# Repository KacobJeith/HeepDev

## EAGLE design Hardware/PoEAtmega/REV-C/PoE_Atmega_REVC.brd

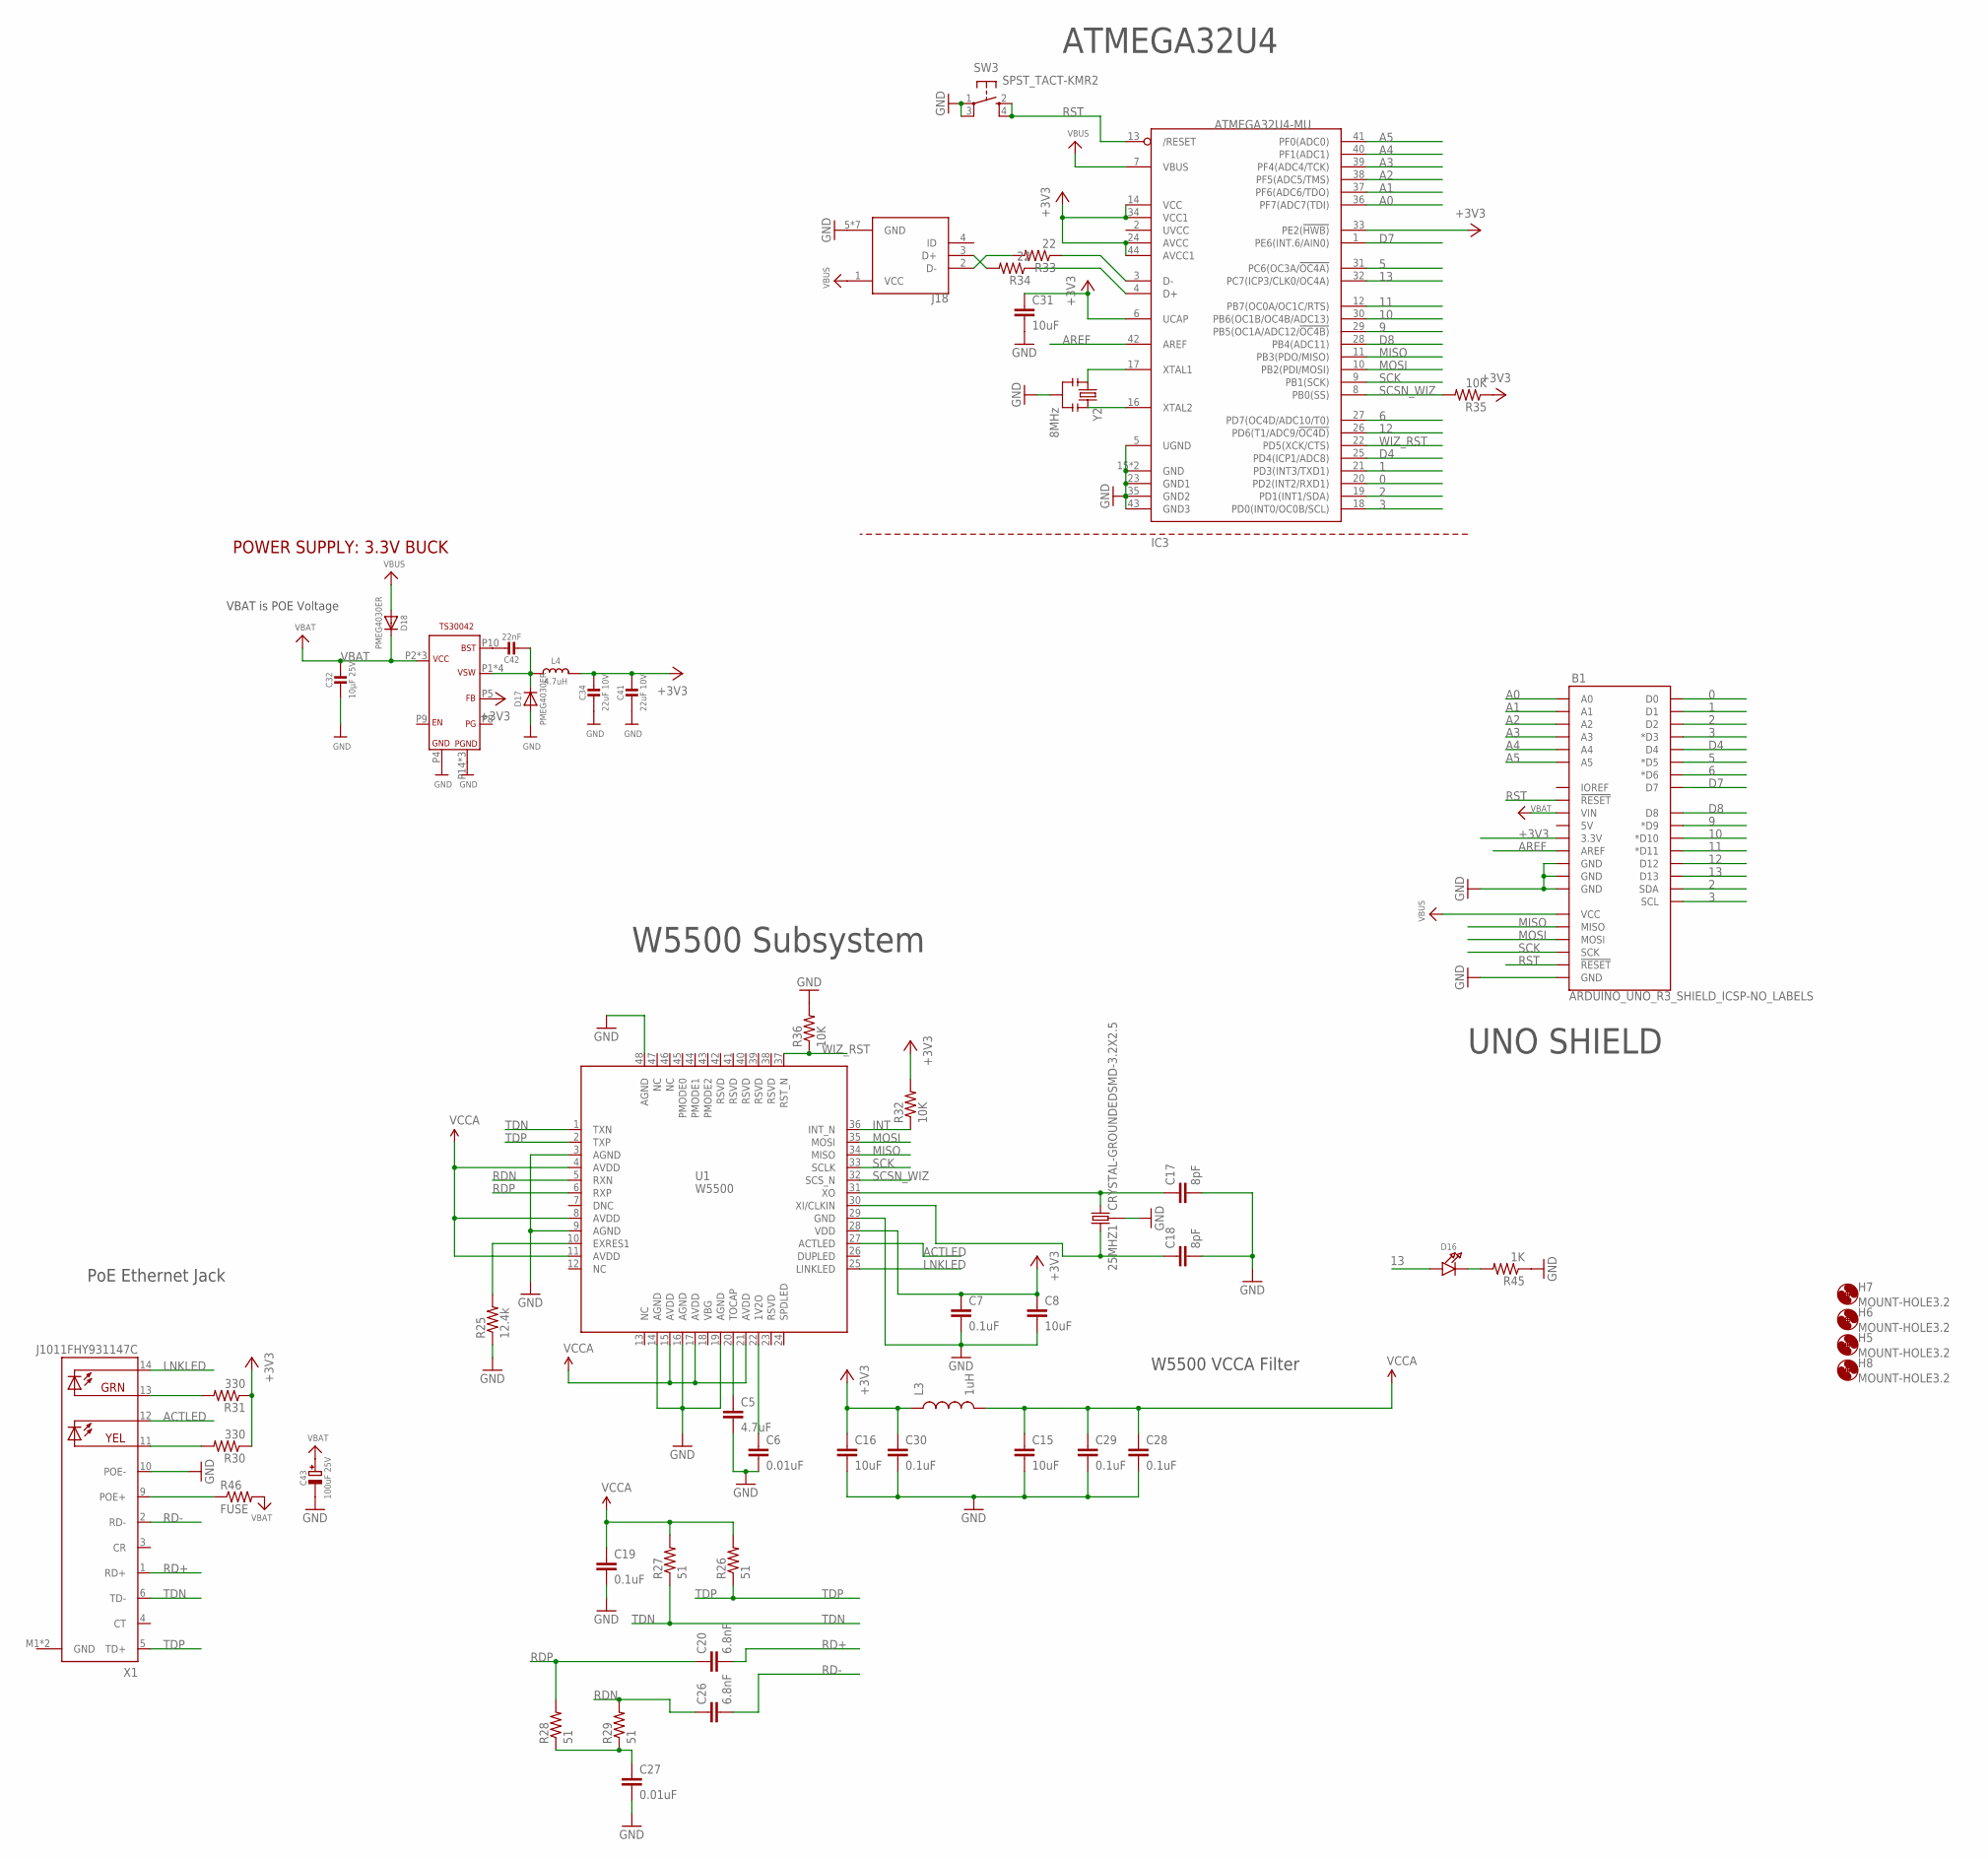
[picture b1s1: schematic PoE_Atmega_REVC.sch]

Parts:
25MHZ1: CRYSTAL-GROUNDEDSMD-3.2X2.5; CRYSTAL-SMD-3.2X2.5MM
B1: ARDUINO_UNO_R3_SHIELD_ICSP-NO_LABELS; UNO_R3_SHIELD_ICSP_NOLABELS
C5: 4.7uF; 0603-CAP
C6, C27: 0.01uF; 0603-CAP
C7, C19, C28, C29, C30: 0.1uF; 0603-CAP
C8, C15, C16, C31: 10uF; 0603-CAP
C17, C18: 8pF; 0603-CAP
C20, C26: 6.8nF; 0603-CAP
C32: 10µF 25V; 0603-MINI
C34, C41: 22uF 10V; 0603-MINI
C42: 22nF; 0603-MINI
C43: 100uF 25V; PANASONIC_D
D16: LED0805_NOOUTLINE; CHIPLED_0805_NOOUTLINE
D17, D18: PMEG4030ER; SOD-123
H5, H6, H7, H8: MOUNT-HOLE3.2; 3,2
IC3: ATMEGA32U4-MU; TQFN44_7MM
J18: 10103594-0001LF; FCI_10103594-0001LF
L3: 1uH; 0603
L4: 4.7uH; INDUCTOR_5X5MM_TDK_VLC5045
R25: 12.4k; 0603-RES
R26, R27, R28, R29: 51; 0603-RES
R30, R31: 330; 0603-RES
R32, R35, R36: 10K; 0603-RES
R33, R34: 22; 0603-RES
R45: 1K; 0603-RES
R46: FUSE; 0603-RES
SW3: SPST_TACT-KMR2; KMR2
U1: W5500
U$44: BUCK_CONVERTER; QFN-16
X1: J1011FHY931147C; HANRUN_POE
Y2: 8MHz; RESONATOR-SMD

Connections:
0: B1.RX (D0), IC3.20 (PD2(INT2/RXD1))
1: B1.TX (D1), IC3.21 (PD3(INT3/TXD1))
2: B1.D2, B1.SDA, IC3.19 (PD1(INT1/SDA))
3: B1.D3 (*D3), B1.SCL, IC3.18 (PD0(INT0/OC0B/SCL))
5: B1.D5 (*D5), IC3.31 (PC6(OC3A/!OC4A))
6: B1.D6 (*D6), IC3.27 (PD7(OC4D/ADC10/T0))
9: B1.D9 (*D9), IC3.29 (PB5(OC1A/ADC12/!OC4B))
10: B1.D10 (*D10), IC3.30 (PB6(OC1B/OC4B/ADC13))
11: B1.D11 (*D11), IC3.12 (PB7(OC0A/OC1C/RTS))
12: B1.D12, IC3.26 (PD6(T1/ADC9/!OC4D))
13: B1.D13, D16.A, IC3.32 (PC7(ICP3/CLK0/OC4A))
+3V3: B1.3.3V, C7.1, C8.1, C16.1, C30.1, C31.1, C34.1, C41.1, IC3.6 (UCAP), IC3.14 (VCC), IC3.24 (AVCC), IC3.33 (PE2(!HWB)), IC3.34 (VCC1), IC3.44 (AVCC1), L3.1, L4.P$2 (2), R30.1, R31.1, R32.2, R35.1, U1.28 (VDD), U$44.P5 (FB)
A0: B1.A0, IC3.36 (PF7(ADC7(TDI))
A1: B1.A1, IC3.37 (PF6(ADC6/TDO))
A2: B1.A2, IC3.38 (PF5(ADC5/TMS))
A3: B1.A3, IC3.39 (PF4(ADC4/TCK))
A4: B1.A4, IC3.40 (PF1(ADC1))
A5: B1.A5, IC3.41 (PF0(ADC0))
ACTLED: U1.27 (ACTLED), X1.12 (YEL-C)
AREF: B1.AREF, IC3.42 (AREF)
D4: B1.D4, IC3.25 (PD4(ICP1/ADC8))
D7: B1.D7, IC3.1 (PE6(INT.6/AIN0))
D8: B1.D8, IC3.28 (PB4(ADC11))
D+2: IC3.4 (D+), R34.1
D-2: IC3.3 (D-), R33.1
GND: 25MHZ1.2 (3), 25MHZ1.4 (3), B1.GND@0 (GND), B1.GND@1 (GND), B1.GND@2 (GND), B1.GND_ICSP (GND), C5.2, C6.2, C7.2, C8.2, C15.2, C16.2, C17.2, C18.2, C19.2, C27.2, C28.2, C29.2, C30.2, C31.2, C32.2, C34.2, C41.2, C43.-, D17.A, IC3.5 (UGND), IC3.15 (GND), IC3.23 (GND1), IC3.35 (GND2), IC3.43 (GND3), IC3.THERMAL (GND), J18.5 (GND), J18.P1 (GND), J18.P2 (GND), J18.P3 (GND), J18.P4 (GND), J18.P5 (GND), J18.P6 (GND), R25.1, R36.2, R45.1, SW3.1, SW3.3 (P1), U1.3 (AGND), U1.9 (AGND), U1.14 (AGND), U1.16 (AGND), U1.19 (AGND), U1.29 (GND), U1.48 (AGND), U$44.P4 (GND), U$44.P14 (PGND), U$44.P15 (PGND), U$44.PAD (PGND), X1.10 (POE-), X1.M1 (GND), X1.M2 (GND), Y2.2
INT: R32.1, U1.36 (INT_N)
LNKLED: U1.25 (LINKLED), X1.14 (GRN-C)
MISO: B1.MISO, IC3.11 (PB3(PDO/MISO)), U1.34 (MISO)
MOSI: B1.MOSI, IC3.10 (PB2(PDI/MOSI)), U1.35 (MOSI)
unnamed: C5.1, U1.20 (TOCAP)
unnamed: C6.1, U1.22 (1V2O)
unnamed: R25.2, U1.10 (EXRES1)
unnamed: C27.1, R28.1, R29.1
unnamed: 25MHZ1.3 (2), C17.1, U1.31 (XO)
unnamed: 25MHZ1.1, C18.1, U1.30 (XI/CLKIN)
unnamed: IC3.16 (XTAL2), Y2.3
unnamed: IC3.17 (XTAL1), Y2.1
unnamed: J18.3 (D+), R34.2
unnamed: J18.2 (D-), R33.2
unnamed: D16.C, R45.2
unnamed: R31.2, X1.13 (GRN-A)
unnamed: R30.2, X1.11 (YEL-A)
unnamed: C42.1, U$44.P10 (BST)
unnamed: C42.2, D17.C, L4.P$1 (1), U$44.P1 (VSW), U$44.P12 (VSW), U$44.P13 (VSW), U$44.P16 (VSW)
unnamed: R46.1, X1.9 (POE+)
RD+: C20.2, X1.1 (RD+)
RD-: C26.2, X1.2 (RD-)
RDN: C26.1, R29.2, U1.5 (RXN)
RDP: C20.1, R28.2, U1.6 (RXP)
RST: B1.RES (!RESET!), B1.RST_ICSP (!RESET!), IC3.13 (/RESET), SW3.2 (S), SW3.4 (S1)
SCK: B1.SCK, IC3.9 (PB1(SCK)), U1.33 (SCLK)
SCSN_WIZ: IC3.8 (PB0(SS)), R35.2, U1.32 (SCS_N)
TDN: R27.1, U1.1 (TXN), X1.6 (TD-)
TDP: R26.1, U1.2 (TXP), X1.5 (TD+)
VBAT: B1.VIN, C32.1, C43.+, D18.C, R46.2, U$44.P2 (VCC), U$44.P3 (VCC), U$44.P11 (VCC)
VBUS: B1.5V_ICSP (VCC), D18.A, IC3.7 (VBUS), J18.1 (VCC)
VCCA: C15.1, C19.1, C28.1, C29.1, L3.2, R26.2, R27.2, U1.4 (AVDD), U1.8 (AVDD), U1.11 (AVDD), U1.15 (AVDD), U1.17 (AVDD), U1.21 (AVDD)
WIZ_RST: IC3.22 (PD5(XCK/CTS)), R36.1, U1.37 (RST_N)

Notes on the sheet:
UNO SHIELD
W5500 Subsystem
W5500 VCCA Filter
PoE Ethernet Jack
ATMEGA32U4
POWER SUPPLY: 3.3V BUCK
VBAT is POE Voltage

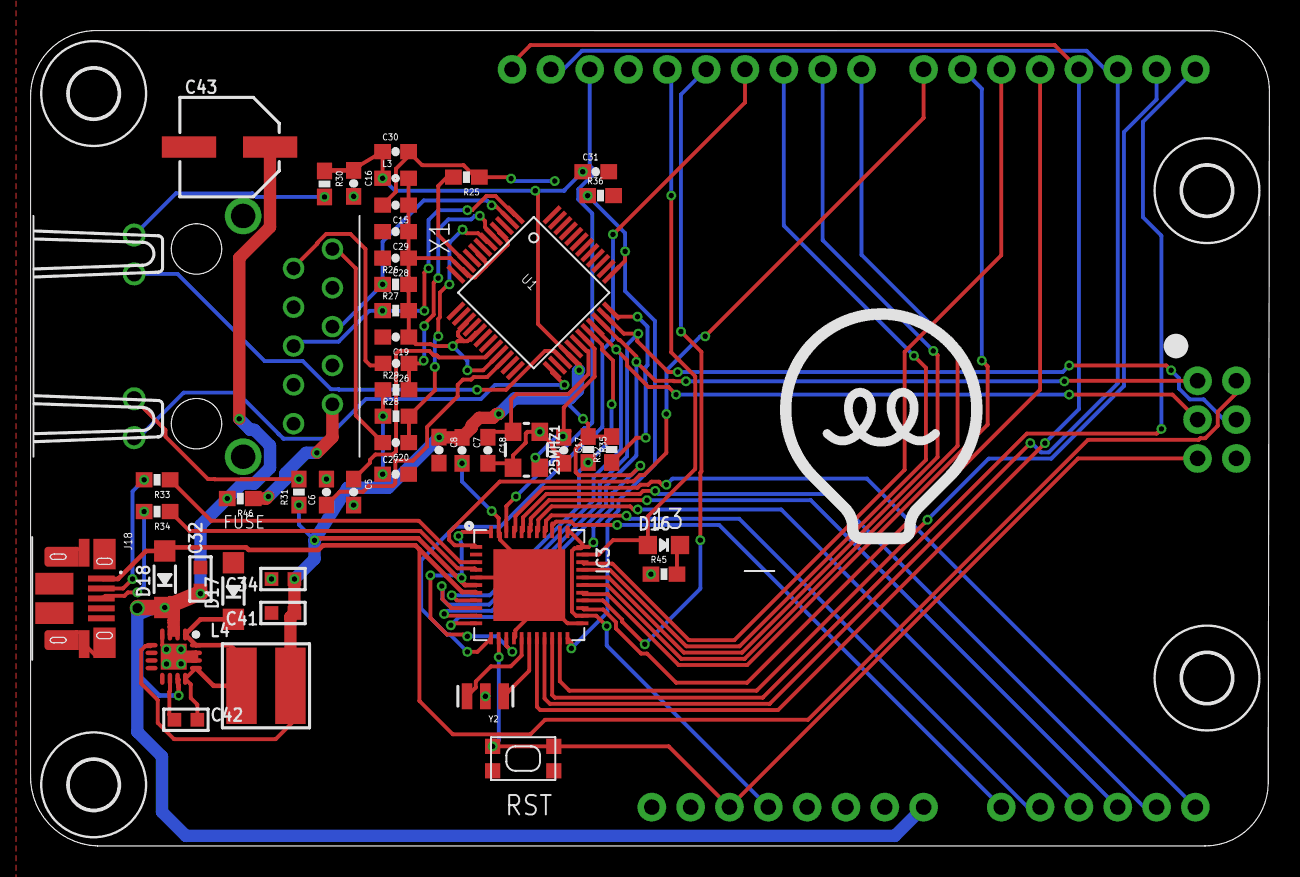
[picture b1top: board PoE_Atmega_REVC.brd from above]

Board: 2 copper layers, 81.0 x 53.3 mm, 54 parts (0 on the bottom side), 59 nets.

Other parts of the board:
U$2: HEEPLOGO

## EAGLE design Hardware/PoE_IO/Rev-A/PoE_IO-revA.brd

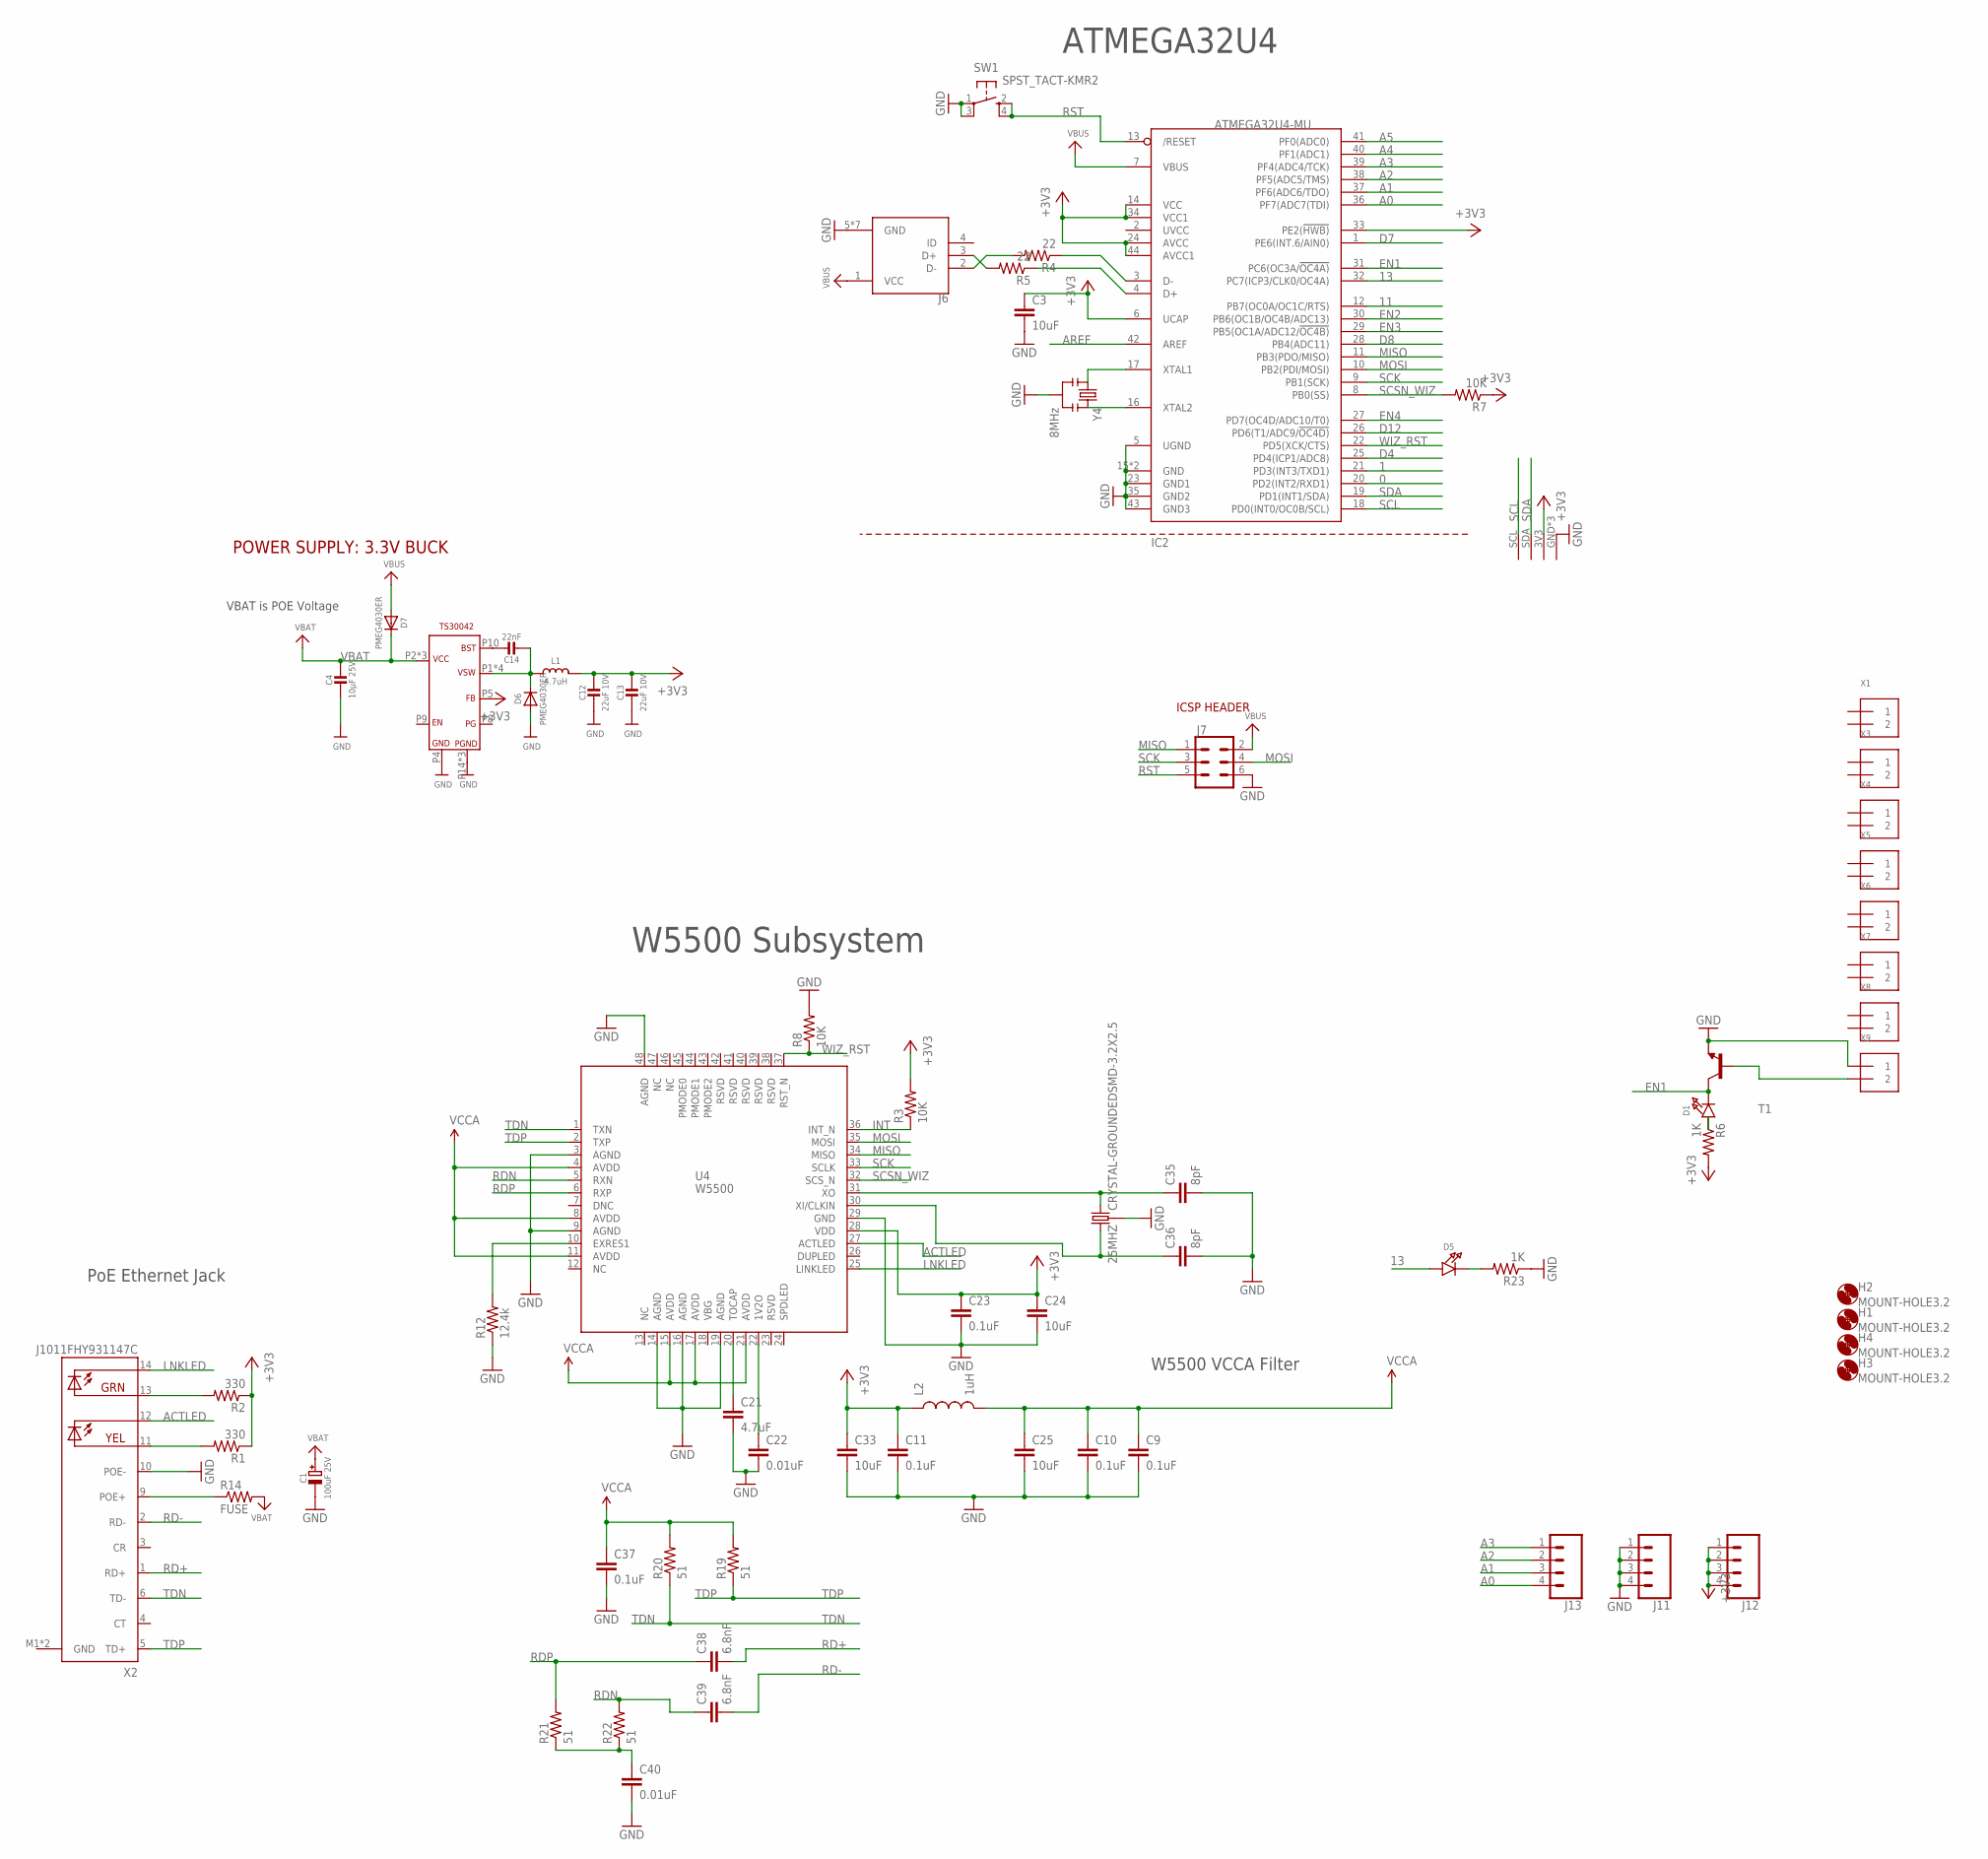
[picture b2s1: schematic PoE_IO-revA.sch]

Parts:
25MHZ: CRYSTAL-GROUNDEDSMD-3.2X2.5; CRYSTAL-SMD-3.2X2.5MM
C1: 100uF 25V; PANASONIC_D
C3, C24, C25, C33: 10uF; 0603-CAP
C4: 10µF 25V; 0603-MINI
C9, C10, C11, C23, C37: 0.1uF; 0603-CAP
C12, C13: 22uF 10V; 0603-MINI
C14: 22nF; 0603-MINI
C21: 4.7uF; 0603-CAP
C22, C40: 0.01uF; 0603-CAP
C35, C36: 8pF; 0603-CAP
C38, C39: 6.8nF; 0603-CAP
D1, D5: LED0805_NOOUTLINE; CHIPLED_0805_NOOUTLINE
D6, D7: PMEG4030ER; SOD-123
H1, H2, H3, H4: MOUNT-HOLE3.2; 3,2
IC2: ATMEGA32U4-MU; TQFN44_7MM
J6: 10103594-0001LF; FCI_10103594-0001LF
J7: CONN_03X2NO_SILK; 2X3-NS
J11, J12: CONN_04; 1X04
J13: CONN_041X04_NO_SILK; 1X04_NO_SILK
L1: 4.7uH; INDUCTOR_5X5MM_TDK_VLC5045
L2: 1uH; 0603
R1, R2: 330; 0603-RES
R3, R7, R8: 10K; 0603-RES
R4, R5: 22; 0603-RES
R6, R23: 1K; 0603-RES
R12: 12.4k; 0603-RES
R14: FUSE; 0603-RES
R19, R20, R21, R22: 51; 0603-RES
SW1: SPST_TACT-KMR2; KMR2
T1: MMBT2222ALT1-NPN-SOT23-BEC; SOT23-BEC
U4: W5500
U$3: 4P_JST_MINI_MICRO; 4P_JST1.0
U$19: BUCK_CONVERTER; QFN-16
X1, X3, X4, X5, X6, X7, X8, X9: TERMBLOCK_1X2; TERMBLOCK_1X2-3.5MM
X2: J1011FHY931147C; HANRUN_POE
Y4: 8MHz; RESONATOR-SMD

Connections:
0: IC2.20 (PD2(INT2/RXD1))
1: IC2.21 (PD3(INT3/TXD1))
11: IC2.12 (PB7(OC0A/OC1C/RTS))
13: D5.A, IC2.32 (PC7(ICP3/CLK0/OC4A))
+3V3: C3.1, C11.1, C12.1, C13.1, C23.1, C24.1, C33.1, IC2.6 (UCAP), IC2.14 (VCC), IC2.24 (AVCC), IC2.33 (PE2(!HWB)), IC2.34 (VCC1), IC2.44 (AVCC1), J12.1, J12.2, J12.3, J12.4, L1.P$2 (2), L2.1, R1.1, R2.1, R3.2, R6.2, R7.1, U4.28 (VDD), U$3.3V3, U$19.P5 (FB)
A0: IC2.36 (PF7(ADC7(TDI)), J13.4
A1: IC2.37 (PF6(ADC6/TDO)), J13.3
A2: IC2.38 (PF5(ADC5/TMS)), J13.2
A3: IC2.39 (PF4(ADC4/TCK)), J13.1
A4: IC2.40 (PF1(ADC1))
A5: IC2.41 (PF0(ADC0))
ACTLED: U4.27 (ACTLED), X2.12 (YEL-C)
AREF: IC2.42 (AREF)
D4: IC2.25 (PD4(ICP1/ADC8))
D7: IC2.1 (PE6(INT.6/AIN0))
D8: IC2.28 (PB4(ADC11))
D12: IC2.26 (PD6(T1/ADC9/!OC4D))
D+: IC2.4 (D+), R5.1
D-: IC2.3 (D-), R4.1
EN1: D1.C, IC2.31 (PC6(OC3A/!OC4A)), T1.C
EN2: IC2.30 (PB6(OC1B/OC4B/ADC13))
EN3: IC2.29 (PB5(OC1A/ADC12/!OC4B))
EN4: IC2.27 (PD7(OC4D/ADC10/T0))
GND: 25MHZ.2 (3), 25MHZ.4 (3), C1.-, C3.2, C4.2, C9.2, C10.2, C11.2, C12.2, C13.2, C21.2, C22.2, C23.2, C24.2, C25.2, C33.2, C35.2, C36.2, C37.2, C40.2, D6.A, IC2.5 (UGND), IC2.15 (GND), IC2.23 (GND1), IC2.35 (GND2), IC2.43 (GND3), IC2.THERMAL (GND), J6.5 (GND), J6.P1 (GND), J6.P2 (GND), J6.P3 (GND), J6.P4 (GND), J6.P5 (GND), J6.P6 (GND), J7.6, J11.1, J11.2, J11.3, J11.4, R8.2, R12.1, R23.1, SW1.1, SW1.3 (P1), T1.E, U4.3 (AGND), U4.9 (AGND), U4.14 (AGND), U4.16 (AGND), U4.19 (AGND), U4.29 (GND), U4.48 (AGND), U$3.GND, U$3.P$4 (GND), U$3.P$5 (GND), U$19.P4 (GND), U$19.P14 (PGND), U$19.P15 (PGND), U$19.PAD (PGND), X2.10 (POE-), X2.M1 (GND), X2.M2 (GND), X9.1, Y4.2
INT: R3.1, U4.36 (INT_N)
LNKLED: U4.25 (LINKLED), X2.14 (GRN-C)
MISO: IC2.11 (PB3(PDO/MISO)), J7.1, U4.34 (MISO)
MOSI: IC2.10 (PB2(PDI/MOSI)), J7.4, U4.35 (MOSI)
unnamed: D1.A, R6.1
unnamed: R14.1, X2.9 (POE+)
unnamed: R2.2, X2.13 (GRN-A)
unnamed: R1.2, X2.11 (YEL-A)
unnamed: T1.B, X9.2
unnamed: J6.3 (D+), R5.2
unnamed: D5.C, R23.2
unnamed: IC2.16 (XTAL2), Y4.3
unnamed: IC2.17 (XTAL1), Y4.1
unnamed: J6.2 (D-), R4.2
unnamed: C14.1, U$19.P10 (BST)
unnamed: C14.2, D6.C, L1.P$1 (1), U$19.P1 (VSW), U$19.P12 (VSW), U$19.P13 (VSW), U$19.P16 (VSW)
unnamed: C21.1, U4.20 (TOCAP)
unnamed: C22.1, U4.22 (1V2O)
unnamed: R12.2, U4.10 (EXRES1)
unnamed: C40.1, R21.1, R22.1
unnamed: 25MHZ.3 (2), C35.1, U4.31 (XO)
unnamed: 25MHZ.1, C36.1, U4.30 (XI/CLKIN)
RD+: C38.2, X2.1 (RD+)
RD-: C39.2, X2.2 (RD-)
RDN: C39.1, R22.2, U4.5 (RXN)
RDP: C38.1, R21.2, U4.6 (RXP)
RST: IC2.13 (/RESET), J7.5, SW1.2 (S), SW1.4 (S1)
SCK: IC2.9 (PB1(SCK)), J7.3, U4.33 (SCLK)
SCL: IC2.18 (PD0(INT0/OC0B/SCL)), U$3.SCL
SCSN_WIZ: IC2.8 (PB0(SS)), R7.2, U4.32 (SCS_N)
SDA: IC2.19 (PD1(INT1/SDA)), U$3.SDA
TDN: R20.1, U4.1 (TXN), X2.6 (TD-)
TDP: R19.1, U4.2 (TXP), X2.5 (TD+)
VBAT: C1.+, C4.1, D7.C, R14.2, U$19.P2 (VCC), U$19.P3 (VCC), U$19.P11 (VCC)
VBUS: D7.A, IC2.7 (VBUS), J6.1 (VCC), J7.2
VCCA: C9.1, C10.1, C25.1, C37.1, L2.2, R19.2, R20.2, U4.4 (AVDD), U4.8 (AVDD), U4.11 (AVDD), U4.15 (AVDD), U4.17 (AVDD), U4.21 (AVDD)
WIZ_RST: IC2.22 (PD5(XCK/CTS)), R8.1, U4.37 (RST_N)

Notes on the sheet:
W5500 Subsystem
W5500 VCCA Filter
PoE Ethernet Jack
ATMEGA32U4
ICSP HEADER
POWER SUPPLY: 3.3V BUCK
VBAT is POE Voltage

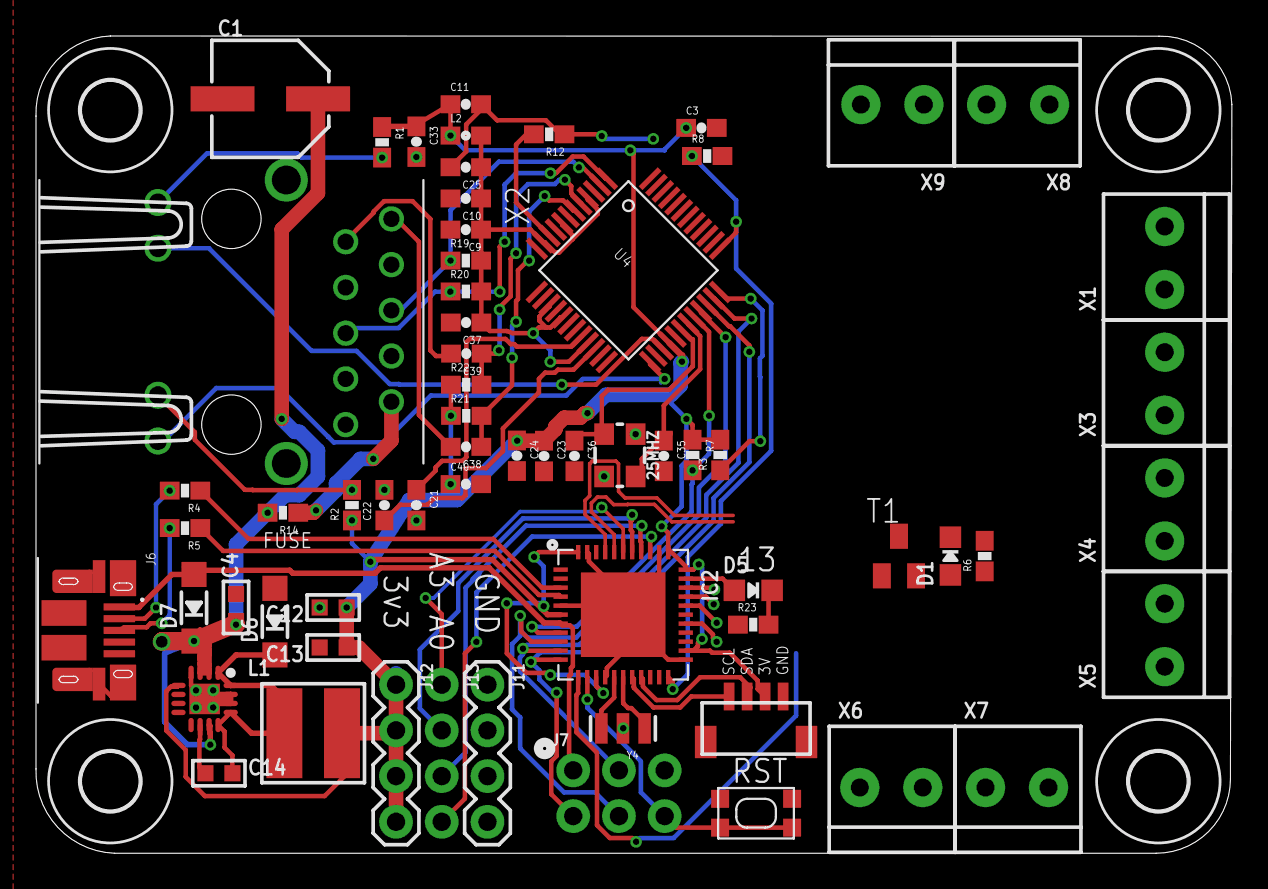
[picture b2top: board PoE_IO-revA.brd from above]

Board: 2 copper layers, 66.4 x 45.4 mm, 69 parts (0 on the bottom side), 48 nets.

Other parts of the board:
U$15: HEEPLOGOSMALL

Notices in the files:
parts and their libraries:
microbuilder: This work is placed in the public domain, and may be freely used for commercial and non-commercial work with the following conditions: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
SparkFun-Passives: Licensing: Creative Commons ShareAlike 4.0 International - https://creativecommons.org/licenses/by-sa/4.0
